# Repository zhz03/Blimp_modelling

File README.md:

# Blimp_modelling

Some links for internal group members:

Project Schedule: https://docs.google.com/document/d/1mM89C8mCaChhVlr7JDBp17N-gWRBhzcNA5U3cbLESRc/edit?usp=sharing

System inputs and outputs: https://docs.google.com/document/d/1VdFgAMIE6IxLuRrdX70nhkSFN5Ng0NW4ozphF4rFDRw/edit

Gazebo simulator: https://github.com/ootang2018/blimp_simulator

Ubuntu 18 ROS ready-to-go version: https://drive.google.com/drive/folders/1pQIc64VEQB58DwDCWm181PesGNF_KXpc

The report link:https://www.overleaf.com/read/zkyzhqtbyvvk

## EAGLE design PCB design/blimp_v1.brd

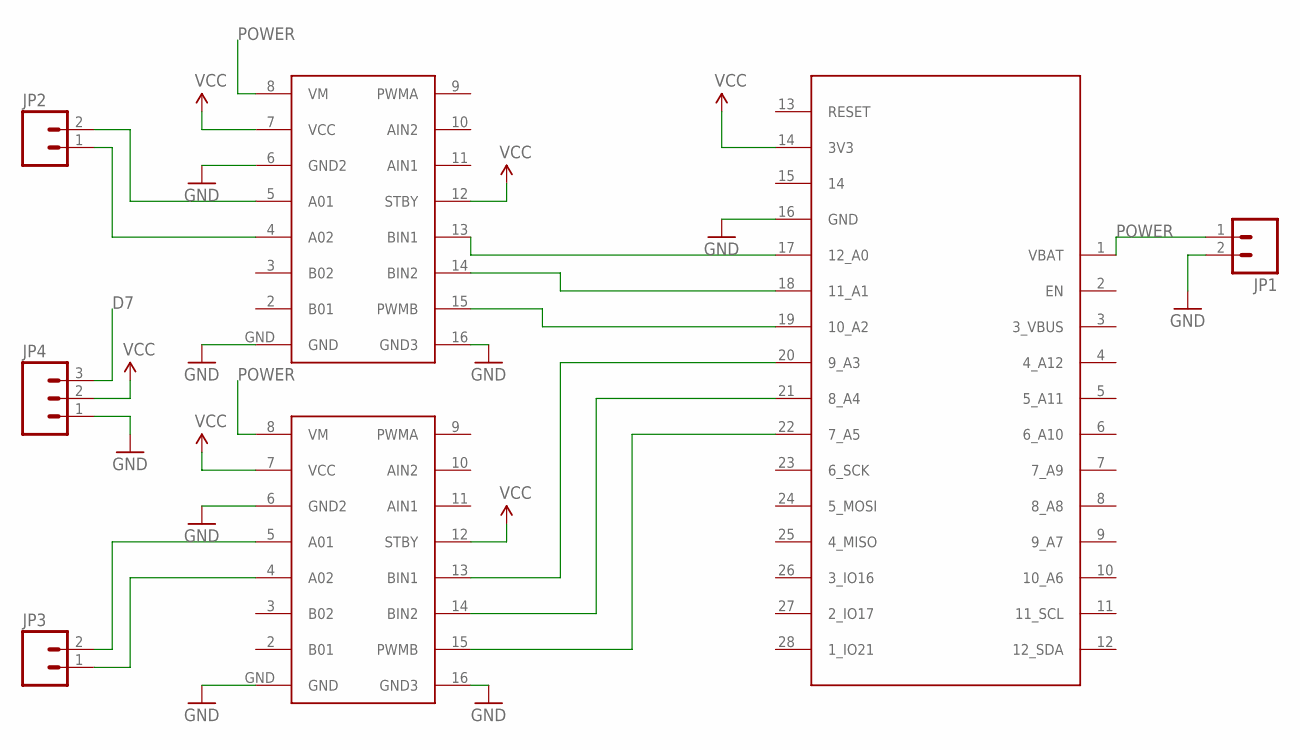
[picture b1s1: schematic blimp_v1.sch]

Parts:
JP1: M02-JST-2MM-SMT; JST-2-SMD
JP2, JP3: M02PTH; 1X02
JP4: M03PTH; 1X03
U$1: ESP32
U$2, U$4: TB6612

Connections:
A0: U$1.17 (12_A0), U$4.13 (BIN1)
D7: JP4.3
GND: JP1.2, JP4.1, U$1.16 (GND), U$2.6 (GND2), U$2.16 (GND3), U$2.GND, U$4.6 (GND2), U$4.16 (GND3), U$4.GND
unnamed: JP2.2, U$4.5 (A01)
unnamed: JP2.1, U$4.4 (A02)
unnamed: JP3.2, U$2.5 (A01)
unnamed: JP3.1, U$2.4 (A02)
unnamed: U$1.18 (11_A1), U$4.14 (BIN2)
unnamed: U$1.19 (10_A2), U$4.15 (PWMB)
unnamed: U$1.20 (9_A3), U$2.13 (BIN1)
unnamed: U$1.21 (8_A4), U$2.14 (BIN2)
unnamed: U$1.22 (7_A5), U$2.15 (PWMB)
POWER: JP1.1, U$1.1 (VBAT), U$2.8 (VM), U$4.8 (VM)
VCC: JP4.2, U$1.14 (3V3), U$2.7 (VCC), U$2.12 (STBY), U$4.7 (VCC), U$4.12 (STBY)

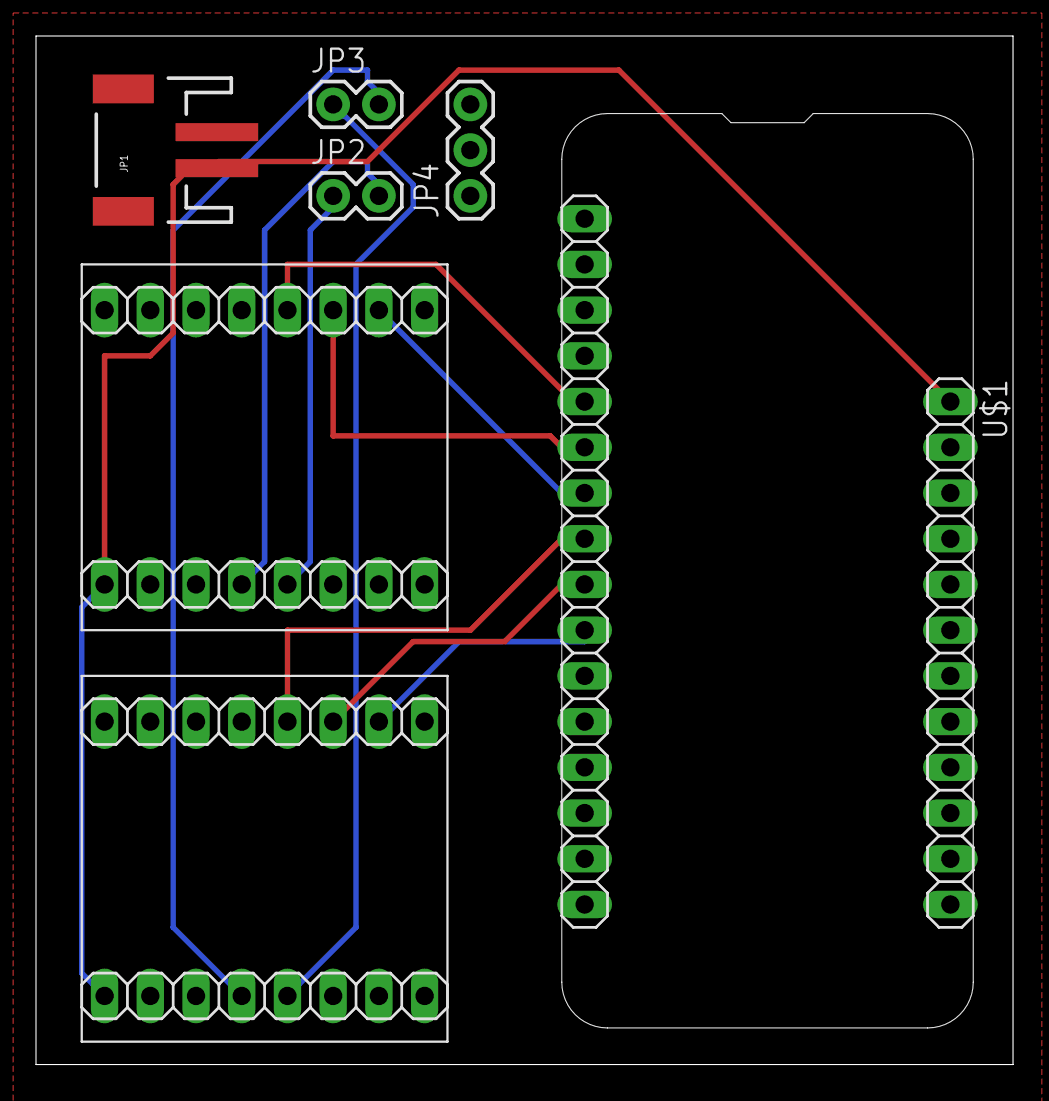
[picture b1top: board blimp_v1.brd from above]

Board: 2 copper layers, 54.3 x 57.1 mm, 7 parts (0 on the bottom side), 13 nets.

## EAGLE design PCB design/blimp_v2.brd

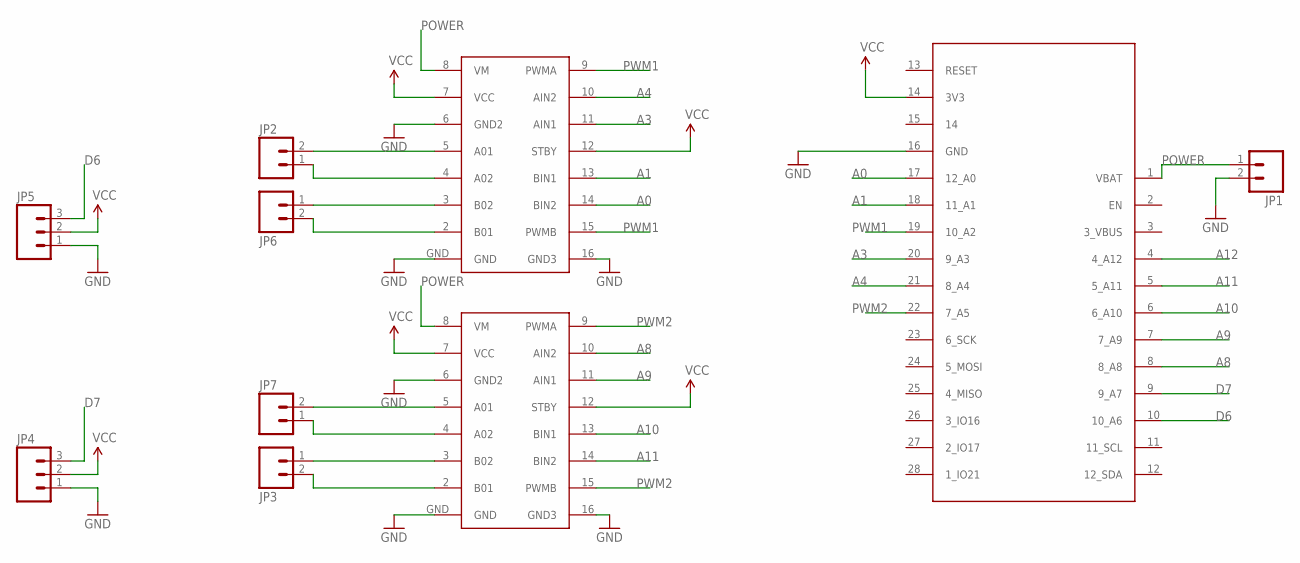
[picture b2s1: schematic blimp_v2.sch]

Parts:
JP1: M02-JST-2MM-SMT; JST-2-SMD
JP2, JP3, JP6, JP7: M02PTH; 1X02
JP4, JP5: M03PTH; 1X03
U$1: ESP32
U$2, U$4: TB6612

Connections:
A0: U$1.17 (12_A0), U$4.14 (BIN2)
A1: U$1.18 (11_A1), U$4.13 (BIN1)
A3: U$1.20 (9_A3), U$4.11 (AIN1)
A4: U$1.21 (8_A4), U$4.10 (AIN2)
A8: U$1.8 (8_A8), U$2.10 (AIN2)
A9: U$1.7 (7_A9), U$2.11 (AIN1)
A10: U$1.6 (6_A10), U$2.13 (BIN1)
A11: U$1.5 (5_A11), U$2.14 (BIN2)
A12: U$1.4 (4_A12)
D6: JP5.3, U$1.10 (10_A6)
D7: JP4.3, U$1.9 (9_A7)
GND: JP1.2, JP4.1, JP5.1, U$1.16 (GND), U$2.6 (GND2), U$2.16 (GND3), U$2.GND, U$4.6 (GND2), U$4.16 (GND3), U$4.GND
unnamed: JP2.2, U$4.5 (A01)
unnamed: JP2.1, U$4.4 (A02)
unnamed: JP7.2, U$2.5 (A01)
unnamed: JP7.1, U$2.4 (A02)
unnamed: JP6.1, U$4.3 (B02)
unnamed: JP6.2, U$4.2 (B01)
unnamed: JP3.1, U$2.3 (B02)
unnamed: JP3.2, U$2.2 (B01)
POWER: JP1.1, U$1.1 (VBAT), U$2.8 (VM), U$4.8 (VM)
PWM1: U$1.19 (10_A2), U$4.9 (PWMA), U$4.15 (PWMB)
PWM2: U$1.22 (7_A5), U$2.9 (PWMA), U$2.15 (PWMB)
VCC: JP4.2, JP5.2, U$1.14 (3V3), U$2.7 (VCC), U$2.12 (STBY), U$4.7 (VCC), U$4.12 (STBY)

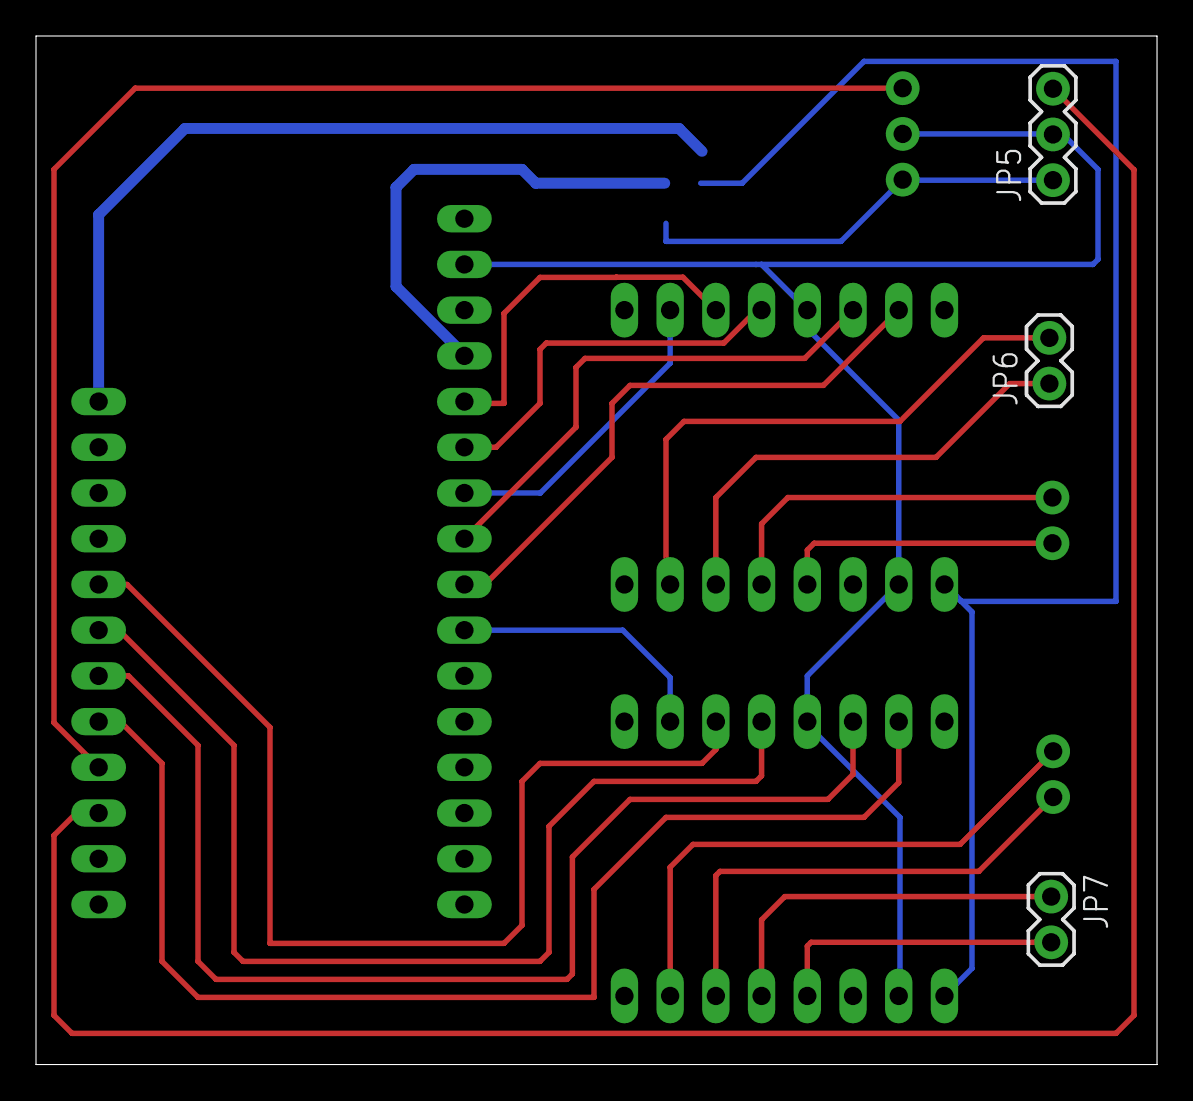
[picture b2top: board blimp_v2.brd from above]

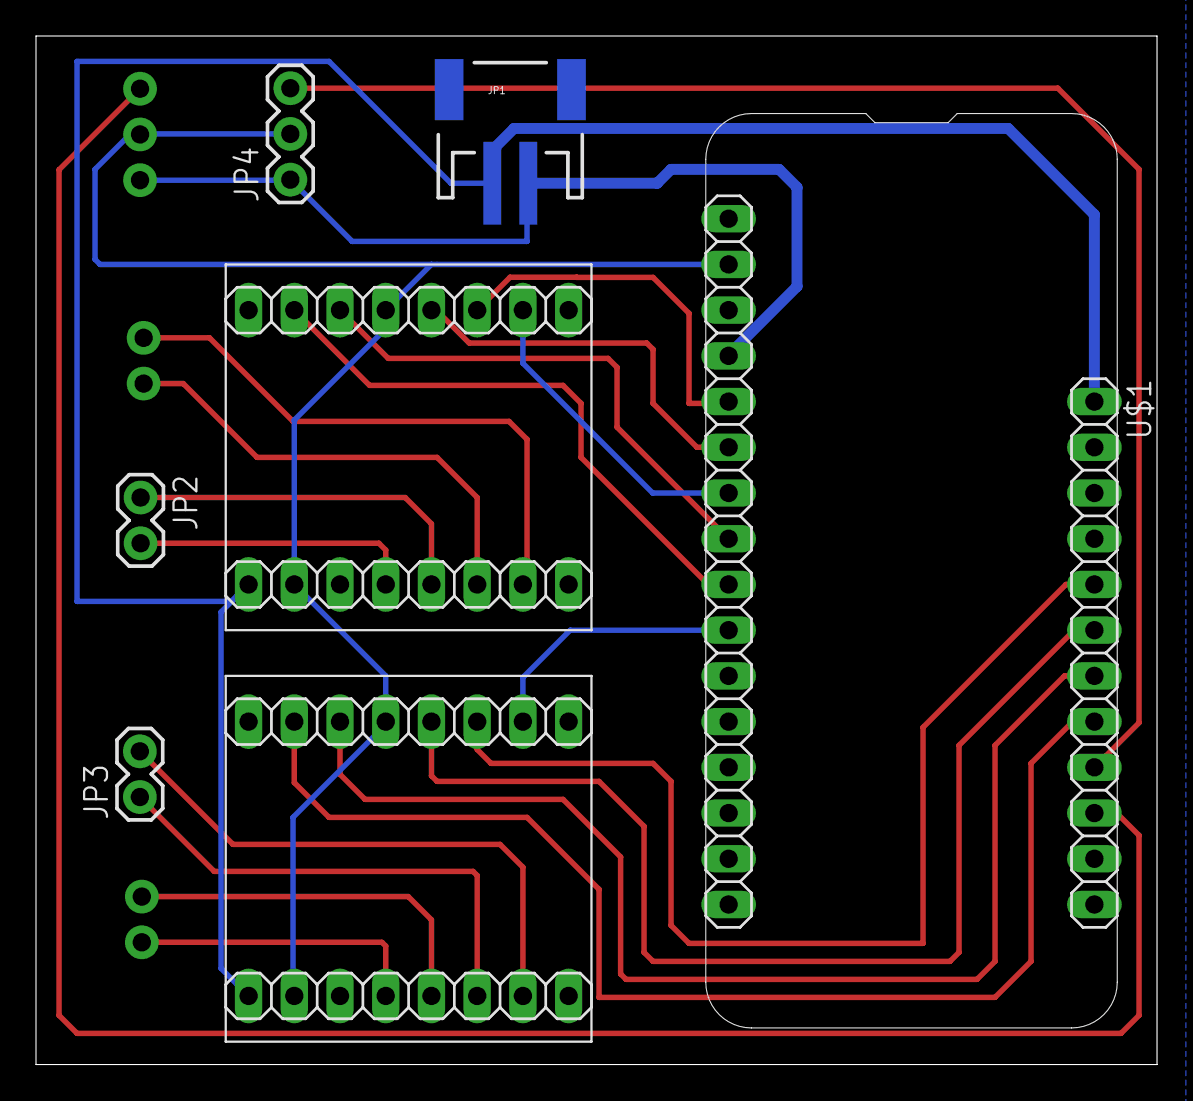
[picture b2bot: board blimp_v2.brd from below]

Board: 2 copper layers, 62.3 x 57.1 mm, 10 parts (7 on the bottom side), 23 nets.

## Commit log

2020-12-02 uploaded some links to the README
2020-12-02 Uploaded project proposal
2020-12-02 added new simulator and VM links to the README
2020-12-03 upload the VMware and ubuntu system tutorial
2020-12-07 使用 Colaboratory 创建
2020-12-10 Move all the code to the code folder
2020-12-10 upload dynamics integration code to the folder
2020-12-10 uploaded the slides to the folder
2020-12-10 uploaded the report link
2020-12-10 added dynamics model
2020-12-16 updated rotation matrix
2021-01-05 uploaded project plan for winter 2021
2021-01-14 uploaded a week2 agenda
2021-01-15 meeting notes
2021-01-18 move to a new folder
2021-01-18 uploaded my weekly plan
2021-01-18 Create Ethan FORAY Overleaf Link
2021-01-18 added Kyle's Week 3 plan
2021-01-20 uploaded Ethan's week 3 plan
2021-01-20 updated week3 meeting agenda
2021-01-21 uploaded the agenda after meeting
2021-01-21 correct some typo
2021-01-21 fix typo
2021-01-22 uploaded the new Friday meeting agenda
2021-01-22 add a new agenda
2021-01-25 update the meeting agenda for week4
2021-01-26 add meeting content into the meeting agenda
2021-01-29 update Friday meeting content
2021-02-01 Week5 meeting agenda
2021-02-01 Zhaoliang's plan for week5
2021-02-09 uploaded week 5 meeting note
2021-02-09 upload zhaoliang's plan for the week
2021-02-09 upload the week6 meeting agenda
2021-02-09 added Lei's week6 plan
2021-02-09 uploaded the dimension_shape python code
2021-02-10 updated meeting agenda
2021-02-10 added restructured evaluator code
2021-02-15 Auto stash before merge of "main" and "origin/main"
2021-02-15 upload bibtext file
2021-02-15 upload week7 agenda and plan
2021-02-19 upload the shape dimension code
2021-02-20 Basic Functions
2021-02-20 Minor Bug fixed
2021-02-20 Case I and Case II Completed
2021-02-20 Complete
2021-02-21 Changes Made
2021-02-21 Made Changes
2021-03-09 uploaded the plan for April competition
2021-04-07 upload the manual control code
2021-04-07 Serial Communication
2021-04-07 upload the integrated code
2021-04-07 change the turning angle
2021-05-18 change folder name
2021-05-18 upload plan for summer 2021
2021-06-09 uploaded v1 and v2 of blimp pcb design
2021-06-30 upload the servo test program
2021-06-30 upload the correct servo library
2021-07-07 Test the pinout directly from feather board
2021-07-07 use the example code to test servo parameters
2021-07-07 Read number from Serial monitor
2021-07-07 Fail: Use serial monitor to control servo pos
2021-07-07 Good: control servo pos (hardcode)
2021-07-07 test servo max and min limitation
2021-07-07 success: use simple code to test motor board
2021-07-13 upload test camera program
2021-07-13 upload test_success photo
2021-07-13 finish testing the camera_capture code
2021-07-13 upload image with time on its name
2021-07-13 change the name of saved image to current time
2021-07-13 upload all the random testing images
2021-07-13 change different resolution
2021-07-13 upload 1024_768 random images
2021-07-14 change to save different resolution images
2021-07-14 save random images to random test folder
2021-07-14 run a test
2021-07-14 upload test images, program works
2021-07-14 ready for a series of image capture tasks
2021-07-15 test more than one motor output
2021-07-15 upload blynk control code 1
2021-07-15 the code to test all 4 motors output
2021-07-15 unfinished blynk control code
2021-07-15 upload blynk print info code
2021-07-15 debug and pass the test
2021-07-15 change the name and fix the bug in the program
2021-07-24 test1: servo + motor stack code
2021-07-24 test2: integrate servo + motor with blynk
2021-07-24 modify code to fit esp8266
2021-07-29 test terminal on blynk app
2021-07-29 test sending command to terminal on Blynk
2021-07-29 test the command and show the feedback from serial window
2021-07-29 add error reminder on the terminal
2021-07-29 Finish the f/b/u/d adjustment
2021-07-31 Simplify the code
2021-08-01 This version works
2021-08-01 debug function: it works
2021-08-01 change the program name
2021-08-01 test the left and right confirmation command
2021-08-01 test and left and right command and works well
2021-08-01 Test previous functions under the new command
2021-08-01 fix bugs
2021-08-01 it works!
2021-08-02 add an operation to do distance experiment
2021-08-02 add some random test result from distance experiment
2021-08-02 add the data link
2021-08-02 add google drive link
2021-08-03 add previous code to the evaluation system
2021-08-04 add motion primitive checker code
2021-08-19 format it a little bit
2021-10-05 change the code to adapt to the new configuration for testing purposes
2021-10-09 new test motor code

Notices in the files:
parts and their libraries:
SparkFun: Licensing: CC v3.0 Share-Alike You are welcome to use this library for commercial purposes.
SparkFun-Aesthetics: Licensing: Creative Commons ShareAlike 4.0 International - https://creativecommons.org/licenses/by-sa/4.0
